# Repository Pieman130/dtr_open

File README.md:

More info in wiki: [DTR Wiki](https://github.iu.edu/DTR/dtr/wiki)

`blimpy.py` is the main Blimp script

`IMU_test.py` to run simple tests to ensure BNO055 IMU is functioning

`LIDAR_test.py` tests for TFMini lidar using UART connection

`manual_control.py` to operate blimp with only PS3 controller (no autonomy)  Note: deadman switch is disabled 

**NOTE: the BNO055 library requires two updates:**
1) Ensure software I2C is enabled and HW I2C is disabled on the raspberry pi
	1) modify `/boot/config.txt` to include this line:
	
	`dtoverlay=i2c-gpio,bus=3,i2c_gpio_sda=23,i2c_gpio_scl=24`
	
	2) comment this line out if not already done:

	`dtparam=i2c_arm=on`

2) You may need to modify `bno055.py` to add support for software i2c bus.  On line 196 `self._bus = smbus.SMBus(1)` change the 1 to a 3

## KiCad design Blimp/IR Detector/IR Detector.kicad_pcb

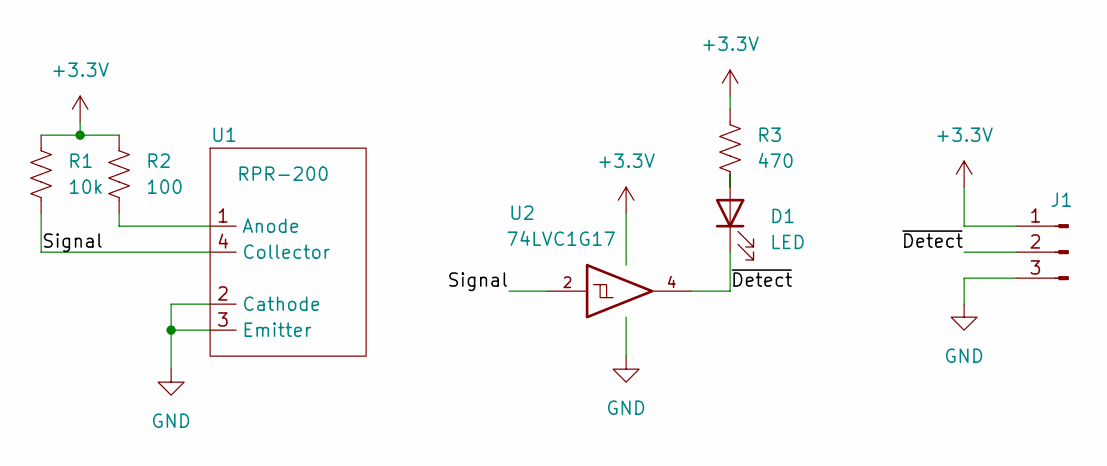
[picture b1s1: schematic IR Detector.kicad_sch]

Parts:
D1: LED; LED_0603_1608Metric_Pad1.05x0.95mm_HandSolder
J1: J1; PinHeader_1x03_P2.54mm_Horizontal
R1: 10k; R_0603_1608Metric_Pad0.98x0.95mm_HandSolder
R2: 100; R_0603_1608Metric_Pad0.98x0.95mm_HandSolder
R3: 470; R_0603_1608Metric_Pad0.98x0.95mm_HandSolder
U1: RPR-200
U2: 74LVC1G17; SOT-23-5

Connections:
+3.3V: J1.1, R1.1, R2.1, R3.1, U2.5 (VCC)
/Signal: R1.2, U1.4 (Collector), U2.2
/~Detect: D1.1 (K), J1.2, U2.4
GND: J1.3, U1.2 (Cathode), U1.3 (Emitter), U2.3 (GND)
unnamed: D1.2 (A), R3.2
unnamed: R2.2, U1.1 (Anode)

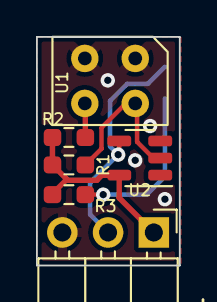
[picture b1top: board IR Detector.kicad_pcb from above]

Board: 2 copper layers, 7.9 x 12.7 mm, 7 parts (1 on the bottom side), 6 nets.

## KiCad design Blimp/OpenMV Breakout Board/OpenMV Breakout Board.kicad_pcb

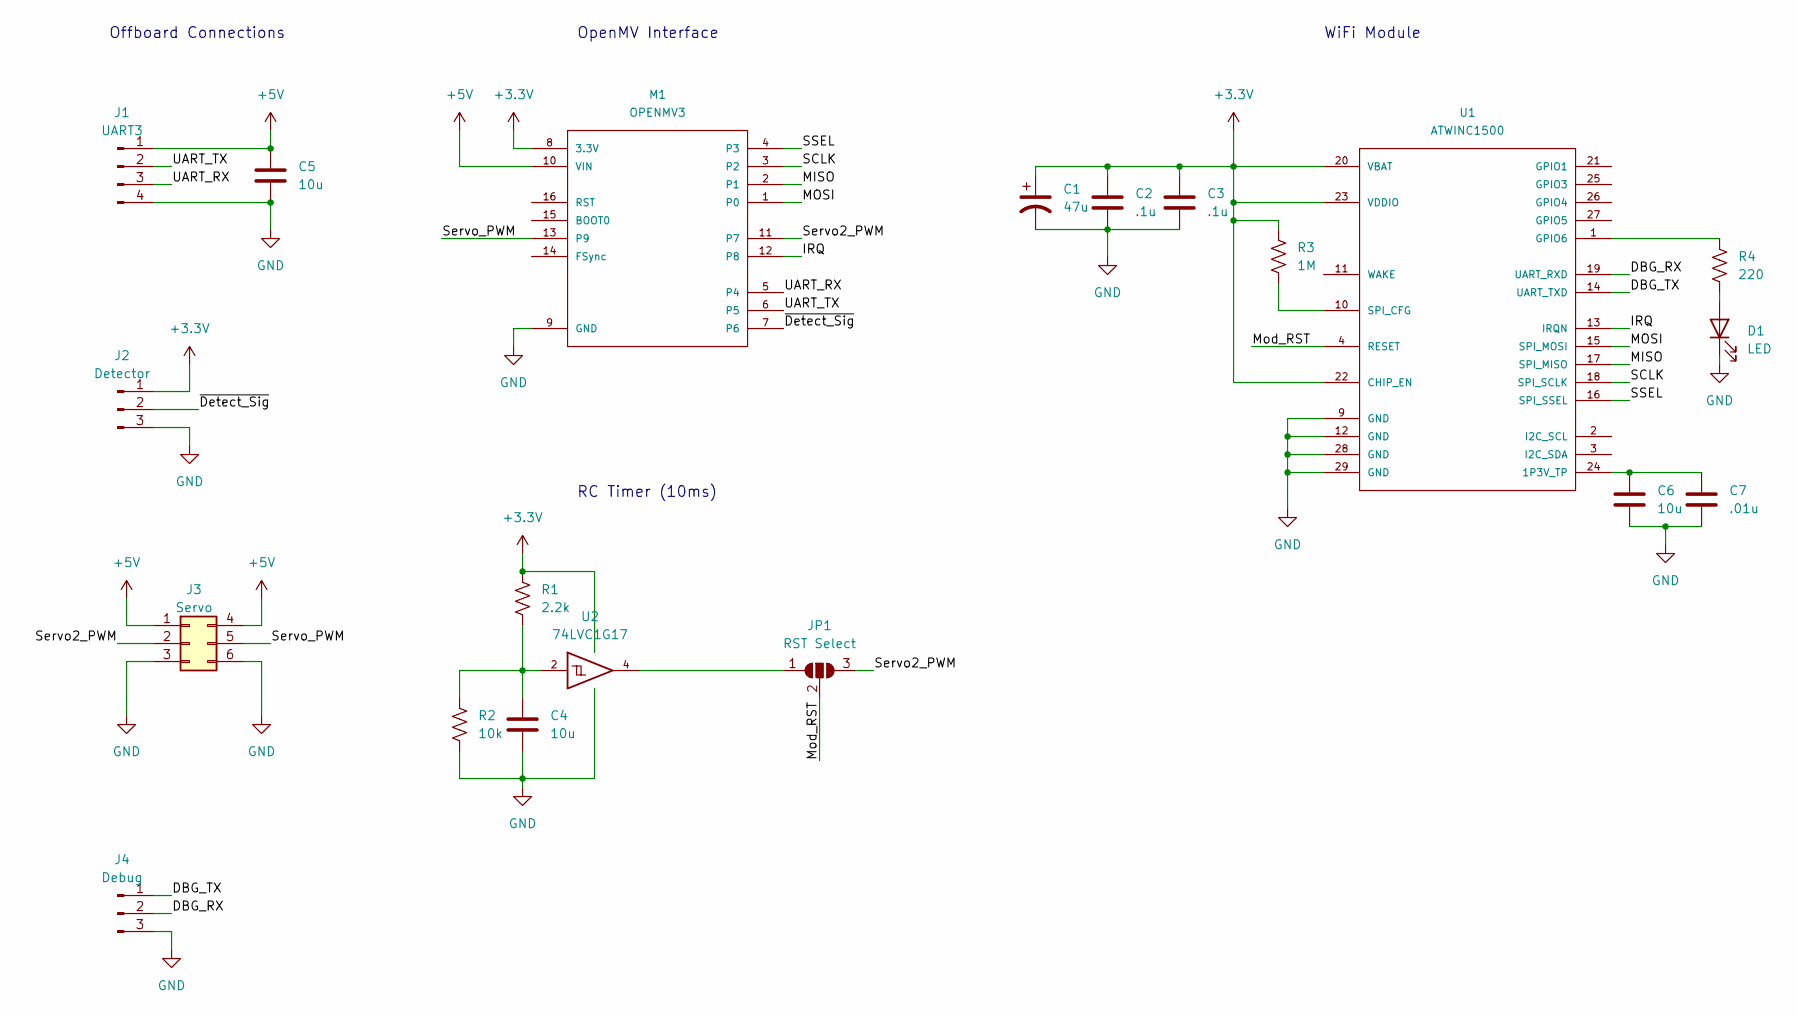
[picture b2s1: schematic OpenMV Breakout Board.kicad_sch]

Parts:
C1: 47u; C_1206_3216Metric_Pad1.33x1.80mm_HandSolder
C2, C3: .1u; C_0603_1608Metric_Pad1.08x0.95mm_HandSolder
C4, C6: 10u; C_0603_1608Metric_Pad1.08x0.95mm_HandSolder
C5: 10u; C_0805_2012Metric_Pad1.18x1.45mm_HandSolder
C7: .01u; C_0603_1608Metric_Pad1.08x0.95mm_HandSolder
D1: LED; LED_0603_1608Metric_Pad1.05x0.95mm_HandSolder
J1: UART3; PinHeader_1x04_P2.54mm_Horizontal
J2: Detector; PinHeader_1x03_P2.54mm_Horizontal
J3: Servo; PinHeader_2x03_P2.54mm_Horizontal
J4: Debug; PinHeader_1x03_P2.54mm_Vertical
JP1: RST Select; SolderJumper-3_P1.3mm_Open_RoundedPad1.0x1.5mm_NumberLabels
M1: OPENMV3
R1: 2.2k; R_0603_1608Metric_Pad0.98x0.95mm_HandSolder
R2: 10k; R_0603_1608Metric_Pad0.98x0.95mm_HandSolder
R3: 1M; R_0603_1608Metric_Pad0.98x0.95mm_HandSolder
R4: 220; R_0603_1608Metric_Pad0.98x0.95mm_HandSolder
U1: ATWINC1500
U2: 74LVC1G17; TSOT-23-5_HandSoldering

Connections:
+3.3V: C1.1, C2.1, C3.1, J2.1, M1.8 (3.3V), R1.1, R3.1, U1.20 (VBAT), U1.22 (CHIP_EN), U1.23 (VDDIO), U2.5 (VCC)
+5V: C5.1, J1.1, J3.1, J3.4, M1.10 (VIN)
/DBG_RX: J4.2, U1.19 (UART_RXD)
/DBG_TX: J4.1, U1.14 (UART_TXD)
/IRQ: M1.12 (P8), U1.13 (IRQN)
/MISO: M1.2 (P1), U1.17 (SPI_MISO)
/MOSI: M1.1 (P0), U1.15 (SPI_MOSI)
/Mod_RST: JP1.2 (C), U1.4 (RESET)
/SCLK: M1.3 (P2), U1.18 (SPI_SCLK)
/SSEL: M1.4 (P3), U1.16 (SPI_SSEL)
/Servo2_PWM: J3.2, JP1.3 (B), M1.11 (P7)
/Servo_PWM: J3.5, M1.13 (P9)
/UART_RX: J1.3, M1.5 (P4)
/UART_TX: J1.2, M1.6 (P5)
/~Detect_Sig: J2.2, M1.7 (P6)
GND: C1.2, C2.2, C3.2, C4.2, C5.2, C6.2, C7.2, D1.1 (K), J1.4, J2.3, J3.3, J3.6, J4.3, M1.9 (GND), R2.2, U1.9 (GND), U1.12 (GND), U1.28 (GND), U1.29 (GND), U2.3 (GND)
unnamed: C4.1, R1.2, R2.1, U2.2
unnamed: C6.1, C7.1, U1.24 (1P3V_TP)
unnamed: D1.2 (A), R4.2
unnamed: JP1.1 (A), U2.4
unnamed: R3.2, U1.10 (SPI_CFG)
unnamed: R4.1, U1.1 (GPIO6)

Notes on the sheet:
WiFi Module
Offboard Connections
RC Timer (10ms)
OpenMV Interface

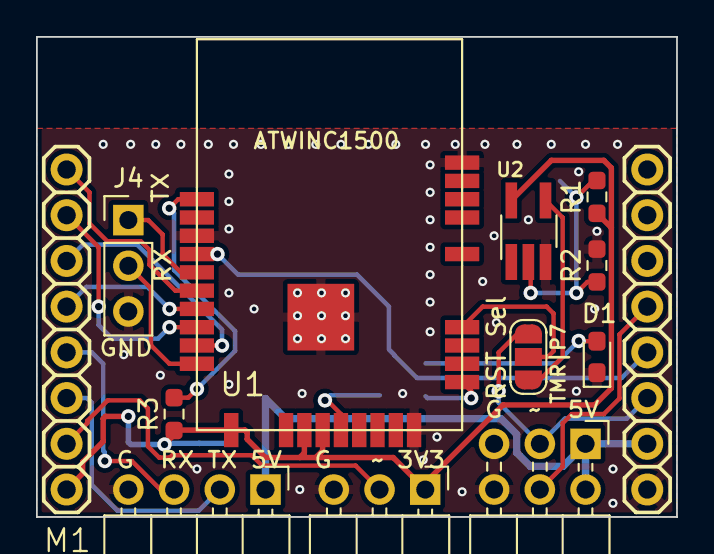
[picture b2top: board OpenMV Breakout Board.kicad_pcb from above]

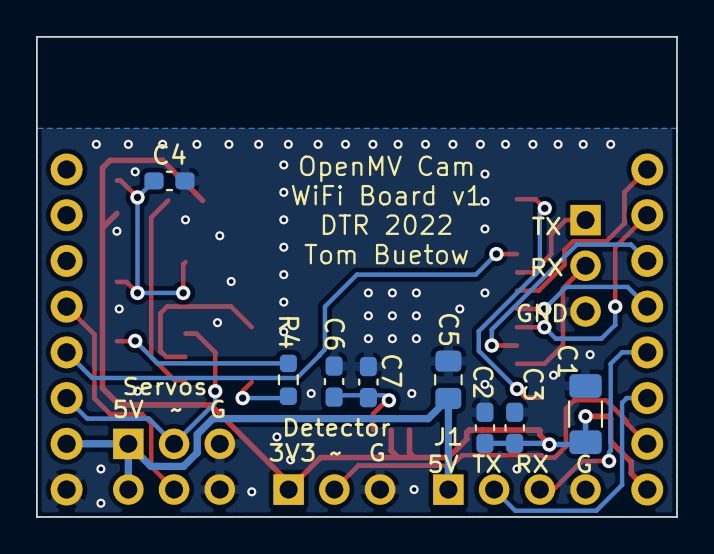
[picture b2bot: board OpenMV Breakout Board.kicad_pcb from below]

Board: 2 copper layers, 35.6 x 26.7 mm, 20 parts (8 on the bottom side), 22 nets.

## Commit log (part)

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2022-03-24 initial commit from other project
2022-05-19 added OpenMV uPython
2022-05-19 ground control initial commit. server to receive messages w/ js test code works. micropython code ready to test with openMV camera once the wifi module is here. urequests library appears to work, but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
2022-05-20 iniital reorganizing code files into ground control and blimp
2022-05-20 ground control <-> openmv status message working
2022-05-20 Ardupilot working with 3D motor control and differential thrust on ch 1, 2
2022-05-23 adding field for basic display of camera detection info
2022-05-23 changes made for quick demo to Adam for UI
2022-05-23 added basic mavlink message flow
2022-05-27 dtr: basic main function working. added upload to mv camera and changed folder structure with main.py and support file folder
2022-05-27 fixed path issue with sending message to ground server
2022-06-06 mavlink msg library
2022-08-04 option1 chosen architecture - initial software commit
2022-08-04 added mavlink message for channle override
2022-08-05 refactoring - cleanup main, added empty functions in action engine
2022-08-05 passing ir sensor data to web ui
2022-08-05 april tag works in main loop
2022-08-05 getting ready for throttle forward test
2022-08-05 ready to test sending data
2022-08-05 got simpler version of april tag working
2022-08-05 cleaning up found april tag
2022-08-05 mvlink test messages
2022-08-09 Wiring diagram for IR balloon detection sensor. Connects to OpenMV GPIO.
2022-08-11 Catcher frame to balloon mount 3D files
2022-08-11 unitTestManeuvers working for two test cases. need to integrate with higher system
2022-08-12 incorporated servo control and lidar messages
2022-08-12 unit testing - adding mavlink class to be created in another file
2022-08-12 unit test - adding realistic time checking
2022-08-12 blimp - main file runs again with open mv camera after unit test file path fixes.
2022-08-12 fixed IR sensor. wifi module must be initialized first
2022-08-12 updated mavlink
2022-08-12 added read function
2022-08-12 added reading of servo values
2022-08-12 simple autonomous bench demo
2022-08-12 started on uart read
2022-08-13 IR Detector board
2022-08-19 added dist func
2022-08-19 reading lidar data successfully
2022-08-19 added parsing funciton
2022-08-20 Initial draft of wiring diagram for full blimp
2022-08-21 git ignore to cover python compiled and kicad temp files
2022-08-21 clean up kicad files that are now ignored
2022-08-21 Updates to OpenMV hat to make pin labels more legible on PCB. Change schematic to be A paper sized for printing, reorg for readability
2022-08-21 IR Detector schematic change paper to A size. Add PDFs of schematics and PCBs for IR Detector and OpenMV Hat
2022-08-21 RC Timer verification - oscope screenshot
2022-08-22 significant refactor: setting up so can run main from PC without open MV with simulated inputs from sensors
2022-08-22 refactor: refactoring now runs and connects to server from pc python instance. this shouldn't break connection from openMV camera but I haven't tested it.
2022-08-24 updated parser
2022-08-25 mapped message number to message name
2022-08-25 added gitignore and removed unused files
2022-08-26 refactor: adding minor tweaks per code review
2022-08-27 Interactive BOMs for both IR Detector and OpenMV Hat
2022-08-30 Wiring harness includes lengths based on preliminary measurements
2022-08-31 Moved IR Detector and OpenMV Breakout folders from Blimp/ to Blimp/PCBs
2022-08-31 Change wiring diagram drawio file to "editable png" to allow easy non-drawio viewing/printing
2022-09-02 initialization script works with leds. purple for startup, green for running connected to server, yelowish for not connected to server, red for fail.
2022-09-02 initial commit of pid
2022-09-02 Update wiring diagrams to include connector images, highlighting pin 1 Fix reversed order connectors.
2022-09-02 adding system diagram.
2022-09-02 Added a reference folder. Put shortcuts to YT videos in it.
2022-09-08 Configure pixracer to auto-arm and allow safety switch to unsafe
2022-09-08 Configure pixracer servo outputs to pass through rc/mavlink channels directly. This removes need to use Arduplane kinematic model and control algorithms
2022-09-08 Update pixracer system modified sensor offsets since last parameter backup
2022-09-08 Add attitude correction to LIDAR distance processing
2022-09-09 adding pid tune values to server control messages
2022-09-09 Map RC controller funtions/channels to blimp functions
2022-09-09 added lidar
2022-09-09 Added multi-platform mocking support and IMU mocking
2022-09-09 minor fix to sensors
2022-09-14 Update wiring with battery connector breakout Improve terminology consistency
2022-09-16 refactor: adding flight director and mission commander classes to control craft.
2022-09-16 hack to get system running ignoring some sensors for now
2022-09-16 added door functions to hw
2022-09-16 fixed collectData when no data is avaialable
2022-09-16 integration w/ Adam code successful.
2022-09-16 updated door status
2022-09-16 Added switch states to dataClasses.py
2022-09-16 Fixed state implementation
2022-09-19 Finished ParseRCSwitchPositions
2022-09-23 added parts list for current build
2022-09-23 ready to test w/ craft for basic autonomous control
2022-09-23 Finished RC Switch Position code
2022-09-23 older rules
2022-09-23 adding software diagram
2022-09-23 add color of LEDs to diagram
2022-09-30 single file test of servo
2022-09-30 servo door working
2022-09-30 lidar working over mavlink. added fix to typo of mavlink parse. prior to adding logger object
2022-09-30 Fixed paths and general bugfixes
    Prettied path code in main.py, as well as implemented proper pathing for testLogger.py. Additionally, fixed some bugs in MissionCommander.py, imageProcessing.py, and resolved weird merge issue with d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
2022-09-30 updated pid
2022-09-30 added assisted altitude
2022-09-30 Updated 3D models with latest versions
2022-09-30 ImageProcessing.py Correction
    Uploaded correct version of image processing file to find goals and balls. Created a branch to stop conflicts
2022-09-30 lots of merge conflicts and minor bug fixes. printing now the hover pid
2022-09-30 logger now prints all printouts to server
2022-10-01 added ability to print multiple loops of logs to UI per user input
2022-10-01 from last commit
2022-10-02 bug, not reading requestedState from server correctly
2022-10-02 now can send manual commands from web ui
2022-10-07 comment out gnd station for Adam testing
2022-10-07 fixed path in copySupportFiles and added limits to pid output
2022-10-07 added test.params
2022-10-07 Update wire diagram to note odd color coding of catch servo connector.
2022-10-07 Fix manual mode
2022-10-07 Added metrics data
    Added photos and videos of quantitative testing of ball detection and goal detection based off of color.
2022-10-07 making progress testing pid
2022-10-07 Image Processing Team's 2022 Plan
    Added control flow diagrams for image processing
2022-10-14 1200 Photos of Yellow Goals (zipped)
    Uploaded a zip file of the 1200 images of the goal taken from three videos at the ledge of the High Bay. Videos may be used to train potential CNN for goal edge detection.
2022-10-21 Initial assembly photos
2022-10-21 manual control works again
2022-10-21 OpenMV test file for camera testing
    Added openMV IDE test file
2022-10-21 Battery cable updates
2022-10-28 adding extra fields to logging
2022-10-28 UI ready to test w/ new config values
2022-10-28 added EMA to lidar measurement
2022-10-28 trying repeat_servo command
2022-10-31 simple motor loop works as expected
2022-11-03 ftp transfer working. now to use rpc to remotely start server
2022-11-03 autonomous test flight success using dumb pid0.
2022-11-03 last state prior to trying pid tuning for real w/ mavlink solved
2022-11-03 now manual remote works again. sends no messages
2022-11-03 remove hack
2022-11-04 progress towards sending files over ftp
2022-11-04 truncating lidar distance
2022-11-04 fixed suppression messages
2022-11-04 ignore
2022-11-04 Added debugging text to processing.py and sensors.py
2022-11-04 implemented rudimentary yaw rate controller
2022-11-04 ready to integrate video processing code
2022-11-04 integrated image processing. not doing anything yet.
2022-11-04 Changes to ImageProcessing.py
2022-11-04 Edited Image_Processing and Created ImageProcessingMainTest
2022-11-04 Reworked image functions for loop issues, fixed sensor resolution in hardware
2022-11-04 use http to get a file, http_update provides a list
2022-11-06 ready for http server concept to transfer files
2022-11-06 file transfer concept finally working wtih node-js http-server and urequests get message. now to send entire support folder
2022-11-06 main example now loads all of support folder
2022-11-06 upload new code to open mv works from button. need to add status text to UI and error text posting from openMV.
2022-11-06 fixed error loop issue
2022-11-06 adding toggle leds when there is an error.
2022-11-06 ignore, but this should have already been ignored
2022-11-06 and the capture script
2022-11-06 remove and ignore .DS_Store
2022-11-07 switch now updates UI correctly
2022-11-07 Changes and commits to image imageProcessing functions
2022-11-07 yaw testing in progress
2022-11-07 added yaw rate limits to PID
2022-11-07 updates to switching
2022-11-07 fixed conversion error
2022-11-07 yaw pid runs, but not seeming to do anything
2022-11-07 fixed rounding error
2022-11-07 Door fix
2022-11-07 fixed yaw controller. now works!
2022-11-07 fixed switch mode
2022-11-07 changed image processing functions to utilize seperate variables
2022-11-07 added setupCamera.py to branch
2022-11-07 tuned filters to seperate orange/red and yellow/green
2022-11-07 tuned color filters and adjusted minimum area and pixel thresholds
2022-11-08 setup to run wrapper code again
2022-11-08 auto-assisted now has radio buttons. need to setup autonomous mode.
2022-11-08 added first autonomous mode
2022-11-08 flight data from 11.8.22
2022-11-08 put switch control in the right spot for being used autonomously or not.
2022-11-08 refactored image processing
2022-11-08 catching exceptions from Camera Timeout
2022-11-08 latest code for image processing integrated.
2022-11-08 error trapping for None
2022-11-08 trying to remove NaN from PID output
2022-11-08 Updated variables and functions in imageprocessing to not have conlficting variables
2022-11-08 Updated dataclasses, imageprocessing, and camera setup
2022-11-08 Updated thresholds for colored blob detection
    Used the ledge in the high bay to calibrate the openMV camera for detecting both goals and green ball.
2022-11-08 simplified control authority matrix
2022-11-08 making 1600 or 0 rawDist values keep last value.
2022-11-08 implemented pressure messages
2022-11-09 making status route properly handle garbage input.
2022-11-09 removing breaking changes from Caeden push 11.8. 14:54:04 and 15:03:38.
2022-11-09 missing files meant to add in last commit.
2022-11-09 removing old image processing variables with color and april tags
2022-11-09 bugfix: returning wrong format for maneuver to execute
2022-11-09 added system information to logs
2022-11-09 made autonomous goal seek
2022-11-09 whoops on debugging stuff
2022-11-09 resolve a few more merge issues
2022-11-09 open mv now pushes imu data to logger
2022-11-09 Corrected distance detection of balls/goals
2022-11-09 added mat file from mission planner
2022-11-09 Overhauled ball/goal detection with density
    used blob.density() to differentiate between goals and balloons. NOTE: density percentages are heavily reliant on current THRESHOLDS value.
2022-11-09 merged latest image processing code from branch.
2022-11-10 Overhauled goal detection to use major/minor axes
2022-11-10 added checksum verification
2022-11-10 pushing database schema
2022-11-10 added distance to goal to server.
2022-11-10 yaw worked. now moving to trying to yaw to goal
2022-11-10 updated changes
2022-11-10 added x error, y error for both goals.
2022-11-10 final code used in qualifying run!
2022-11-11 new points doc
